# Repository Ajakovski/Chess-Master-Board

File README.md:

<div align="center">

# A Standalone PCB Chess Board with OnBoard Machine

### _A chess board that sees every piece, lights every move, and thinks alongside you - no external modules required._

</div>

---

# Overview

**Chess Master Board**

With the power of electro-magnetism this master board is capable of reading every move that the players are making. The powerfull chip with the built in machine gives us the power of a ~2000 ELO player that computes the best moves ***within 2 seconds*** and finally the built in RGB LED matrix sends light signals towards the player with the best move suggestions for you to beat every opponent.

A completely standalone project that requires no external connection gives us the ability to use this board anywhere that we want to. Thanks to the sleep-mode option we recieve a massive battery life extention and we can move on with the game just in case if we decided to pause it.

The chess machine follows every official chess rule and it has included every possible recommendation pattern thanks to the RGB LED matrix. Just put the pieces on their starting squares, press the two buttons for a short period of time and ***ENJOYYY***

Built as an open-source hardware product - every schematic, PCB file and line of firmware is available to reproduce, modify and improve.

---

# Zine

<div align="center">

</div>

---

# Motivation

Some people (like me :)) want to play the game in real life but seem to lack the power of quick decision making while they lose to their opponent. Ofcourse you can achieve that on your smartphone or a PC with a helper like stockfish but what if you dont want to use your digital hardware for playing the game???

With that issue on my mind i created **Chess Master Board** with a different concept:

> _What if the board itself was the computer?_

**The helping buddy that you need!** Hidden inside of the medium sized chess board with just a 5 second double hold on the buttons you awake the mastermind that will help you againts any enemy.

The design is inspired by the tactile satisfaction of phisical chess and will to win your opponents while they struggle for survial:

- No screen needed - the board communicates through light
- No IoT connection needed - the engine runs entirely on device
- Shipped and open-sourced product so anyone can build it, modify it and improve it

The project is also an increidible journey into embedded hardware and PCB design for any enthusiast willing to endulge himself into the type of engineering.

---

# Assembly Guide

## Hardware

***Notice: Always follow the order Main→Upper→Clock PCB for assembling the hardware***

***A visual representation of the whole project has been given with the file:***

***If you dont prefer via the files you can always refer to the visual representation via [OnShape](https://cad.onshape.com/documents/13dd493447813ae98dcbc5b6/w/f13770b66ce0189c65580405/e/d896ca2ed77523ba709b8a3c?renderMode=0&uiState=6a33bc9ec68ee69fbb85f0c4).***

```bash
Hardware/FULLY_ASSEMBLED_PROJECT.step
```

### 1. Order the PCBs and 3D Model

Navigate to: (For PCBs)

```bash
Hardware/KiCad/Gerbers/
```

*Upload the included Gerber files to your preferred PCB manufacturer and order the boards.*

Navigate to: (For 3D Model)
```bash
Hardware/3D_Printing/ (Both zip files)
```
Due to github memory restrictions they are split into 2 files. G-code Pieces features the black/white collection of pieces ready for printing and the V3 Chess 3D.zip is equipped with the full set of information and g-code files for printing the board.
There is also a step version of the files from V3 Chess 3D.zip file, use those also if you need them.

*Upload the G-Code files to your preferred manufacturer and order the parts.*

*The latest version is recommended but if you prefer any older version feel free to use it.*

### 2. Order the Components

Whether you want to order it trough a PCBA concept or to solder it manually you should refer to the BOM file.

```bash
Hardware/BOM.csv
Hardware/Component Libraries.zip
```
All of the files for the components are placed into a zip file due to memory constraints.

Order all parts before starting your assembly and sort them out because there will be a lot of them.

### 3. Solder SMD Components

Considering that you have chosen to solder them personally you should follow the following steps:

Start with the smallest SMD passives before moving to ICs (Refer to the schematic alway before soldering):

- All 0402 decoupling capacitors (100nF) across the board
- Bulk capacitors (1μF, 4.7μF, 10μF, 22μF) near power Ics
- USB-C CC resistors (5.1KΩ)
- All signal and bias resistors per schematic

Recommended tools:
- Flux
- A strong soldering iron with a fine-tip
- Tweezers
- Solder paste + hot air
- Helping hands with a magnifying glass

### 4. Solder Power ICs

Solder the power subsystem in order - validate each stage before starting the next:

- **U3** (BQ24074RGT) - Li-Ion charger, VQFN-16. Solder with hot air; confirm EPAD contact/
- **TH1** (NTC thermistor) - battery temperature input for the charger IC
(Notice: If you are unable to find an NTC thermisto, a 10K ohm resistor will work just fine as a subsitude)
- **U4** (TPS61023DRLT) + **1uH1** (XEL4030-102MEC) - 5V boost converter for LED rail.
- **U5** (AP2112K-3.3TRG1) - 3.3V LDO for ESP32 and logic
- **U145, U146** (REUF300) - PTC resettable fuses on power rails
- **U144** (USBLC6-2P6) - USB ESP protection
- **J2** (USB4110GFA) - USB-C receptacle 
- **D1, D2** - charging status LEDs

Verify whether 5V and 3.3V rails are correct before including anything else.

### 5. Solder the Sensor and Shift Register Array

- **U79-U142** - 64x AH1806-W-7 hall effect sensors (SOT-23, active-LOW)
- **U6-U13** - 8 74HC165BQ shift registers (SSOP-16/QFN, daisy chained)
- Verify sensor orientation - pin 1 marker must align with PCB silkscreen

### 6. Solder the LED Array

- **U14-U77** - 64x APA102C RGB LEDs (5050)
- Theese are orientations-sensitive - follow the schematic and confirm the cathode corner marker before placing every row
- Ensure every LED sits completely flat before reflow; a lifted pad will break the entire following part of the chain.

### 7. Solder the Level Shifter

- **U143** (SN74AHCT125D) - bridges the ESP32's 3.3V outputs to the 5V APA102C DATA and CLK lines
- Without this component the APA102C will be under constant failirue.

### 8. Install the ESP32-S3 Module

- Solder **U1** (ESP32-S3-WROOM2) onto its castellated pads.
- The antenna area requires a **15mm keepout zone** on the base PCB - no copper, no vias (except the screw nearby).
- Confirm the via grid under the module makes solid contact with all EPAD ground pads

### 9. Install the Display and Connectors
- **DS2** - 2.23" 128x32 OLED, I²C interface
- **J1/J4 on Main PCB** Samtec ZF1-15-92-X-WT-X board connectors
- **J3 on Upper PCB** Samtec ZF1-15-92-X-WT-X board connectors
- **J7 on Clock PCB** Samtec ZF1-15-92-X-WT-X board connectors

### 10. Install User Interface Components

- **S3, S4** (TL3315NF250Q) - player clock buttons
- **SW2** (Omron B3FS) - Boot button

### 11. Install Battery Holders and Cells

- Solder **BT1, BT2** (Keystone 1043) - 18650 cell holders
- Do not insert cells untill all soldering is fully complete
- Confirm polarity markings on PCB silkscreen before inserting cells

### 12. Assemble the Enclosure

***Materials needed for assembling:***

- 32x Neodymium magnet in circle with dimensions: 20mm diameter x 5mm height
- 6x Neodymium magnet in a rectangle with dimensions 5x10x2mm
- Glue, any type just make sure to get a strong one
- 11x M3 screw nuts (more is fine in case you loose some)
- Notice: If you dont get screws with the OLED screen you will have to acquire them personally

***Steps for assembling***

The main part of the assembling is sticking the magnets in their appropriate places. 
There are 2 places where they should be placed:
- The rectangular magnets should be placed 3x on the lid used for closing the bottom of the chess board where on one side you will find 3 rectangular holes and 3x inside of the chess board where you will the same 3 rectangular insertions. Apply glue inside of them and stick the magnets inside. **BE CAREFUL** and place the pair of three magnets with opposite polarities. So if the closing lid has the north pole facing outwards, make sure to have the south pole facing outwards on the chess board.
- The circular magnets are designated to go into the chess pieces. Same procedure, apply glue and stick them. **Make sure to place the south pole outwards because otherwise the hall effect sensors will have a poor reading**
- Every PCB has their own designated screw holes and how they should be placed. **Every PCB next to the screw hole has the side on where it should be placed.** (for eg. UR- Upper Right, DR - Down Right)
- The Push buttons should be inserted from inside of the chess board before putting the screws on for the Clock PCB so that the buttons stay locked on top of the buttons built-in on the PCB.
- Verify detection by powering the board and placing every piece on their starting square during first boot.

---

## Firmware Installation

### 1. Install ESP-IDF

```bash
git clone --recursive https://github.com/espressif/esp-idf.git ~/esp/esp-idf
cd ~/esp/esp-idf
./install.sh esp32s3
source ./export.sh
```

Follow the [official Espressif guide](https://docs.espressif.com/projects/esp-idf/en/stable/esp32s3/get-started/index.html) for WIndows and macOS variants.

### 2. Clone the Repository

```bash
git clone https://github.com/Ajakovski/chess-master-board.git
cd chess-master-board
cd Firmware
```

### 3. Set Target and Build

```bash
idf.py set-starget esp32s3
idf.py build
```

### 4. Flash the Firmware

Connect via USB-C. If the board does not enter download mode automatically, hold **BOOT** and tap **EN**, then release BOOT.

```bash
# Linux
idf.py -p /dev/tty/USB0 flash

# macOS
idf.py -p /dev/cu.usbserial-XXXX flash

# Windows
idf.py -p COM3 flash
```

### 5. Monitor Serial Output

```bash
idf.py -p /dev/ttyUSB0 monitor
```

Exit with 'Ctrl+]'.

---

# BOM

**If you are refering from the BOM.csv file please use a converter csv to table because it will be hard for you to read the documentation. And as always you can recall from my githubs BOM anytime you want**

| Designator | Function | Value / Part | Package | Qty | Price (USD) | Link |
|---|---|---|---|---|---|---|
| U1 | MCU Module | ESP32-S3-WROOM-2 N32R16V | LCC-54 | 1 | $12 | [Mouser](https://www.mouser.bg/ProductDetail/Espressif-Systems/ESP32-S3-WROOM-2-N32R16V?qs=%252BHhoWzUJg4Kf%2FwmS40wg%252BQ%3D%3D&srsltid=AfmBOopjud5fwNEdPJr_Fcp_F6RRXBi_0mpNTvMmjx49w7TWEqiv5xGV) |
| U79–U142 | Hall Effect Sensor | AH1806-W-7 | SOT-23 | 64 | $20 | [Mouser](https://www.mouser.com/ProductDetail/Diodes-Incorporated/AH1806-W-7?qs=eSfX1CQlHqqRKgthoXGrzg%3D%3D&srsltid=AfmBOoqvt9XKLP8jc6GHH0L_jmNus1_TszQpJJyJu60i3bDtAeJsRl4r) |
| U6–U13 | Shift Register | 74HC165BQ_115 | QFN-17 | 8(10) | $2.21 | [Mouser](https://www.mouser.bg/ProductDetail/Nexperia/74HC165BQ115?qs=P62ublwmbi86viaf9iloMA%3D%3D&srsltid=AfmBOop67e87aW457vff1BOXmou8TWC8JPC6vrp5882xNvyS27eVy15c) |
| U14–U77 | Addressable RGB LED | APA102C | SON-6 (5050) | 64(100) | $10.5 | [AliExpress](https://www.aliexpress.com/item/1005008174203527.html) |
| U143 | Level Shifter | SN74AHCT125DR | SOIC-14 | 1 | $0.46 | [Mouser](https://www.mouser.bg/ProductDetail/Texas-Instruments/SN74AHCT125DR?qs=B7lSdIxWQkm9VQkJOjfRaA%3D%3D) |
| DS2 | OLED Display | 128×32 2.23" I²C | SSD1305 | 1 | $10 | [AliExpress](https://www.aliexpress.com/item/1005008489357042.html?spm=a2g0o.productlist.main.9.1cd31P5n1P5nfd&algo_pvid=10006fad-7505-426f-8c02-2c3dbc745dfc&algo_exp_id=10006fad-7505-426f-8c02-2c3dbc745dfc-8&pdp_ext_f=%7B%22order%22%3A%229%22%2C%22eval%22%3A%221%22%2C%22fromPage%22%3A%22search%22%7D&pdp_npi=6%40dis%21MKD%21567.22%21567.22%21%21%2165.40%2165.40%21%40212e520f17815127163675148eea9b%2112000045367691230%21sea%21MK%210%21ABX%211%210%21n_tag%3A-29910%3Bd%3Aaeed944%3Bm03_new_user%3A-29895&curPageLogUid=1Bi8k4hGK8K7&utparam-url=scene%3Asearch%7Cquery_from%3A%7Cx_object_id%3A1005008489357042%7C_p_origin_prod%3A#nav-description) |
| BT1, BT2 | 18650 Battery Holder | Keystone 1043 | THT | 2 | $6.82 | [Mouser](https://www.mouser.com/ProductDetail/Keystone-Electronics/1043?utm_campaign=mouser&qs=%2F7TOpeL5Mz6j%2FnxeOA1rsg%3D%3D&utm_medium=online&utm_source=snapedaonline&utm_content=modelunipart_id=214578&manufacturer=Keystone) |
| U3 | Li-Ion Charger IC | BQ24074RGT | VQFN-16 | 1 | $2.48 | [Mouser](https://www.mouser.bg/ProductDetail/Texas-Instruments/BQ24074RGTR?qs=ZV%2Fxhq4oszp2Nll7fIx5wg%3D%3D&srsltid=AfmBOopf_GDP2yO0D5PAa7cuepwFxpUxXFdTjUaKyMCHw1c4K6qqB7_Z) |
| U4 | Boost Converter (5V) | TPS61023DRLT | SOT-6 | 1 | $1.4 | [Mouser](https://www.mouser.bg/ProductDetail/Texas-Instruments/TPS61023DRLT?qs=BJlw7L4Cy78Zr3IJIU3gNw%3D%3D) |
| 1uH1 | Power Inductor | XEL4030-102MEC (1µH) | XEL4030 | 1 | $2.17 | [Mouser](https://www.snapeda.com/api/url_track_click_mouser/?unipart_id=4653188&manufacturer=Coilcraft&part_name=XEL4030-102MEC&search_term=None) |
| U5 | 3.3V LDO Regulator | AP2112K-3.3TRG1 | SOT-25 | 1 | $0.25 | [Mouser](https://www.mouser.bg/ProductDetail/Diodes-Incorporated/AP2112K-3.3TRG1?qs=x6A8l6qLYDDPYHosCdzh%2FA%3D%3D) |
| U144 | USB ESD Protection | USBLC6-2P6 | SOT-666 | 1 | $0.63 | [Mouser](https://www.mouser.bg/ProductDetail/STMicroelectronics/USBLC6-2P6?qs=6ARB0lp6jlViGcbUSvj1Mw%3D%3D) |
| U145, U146 | PTC Resettable Fuse | RUEF300 (3A) | Radial | 2 | $1 | [AliExpress](https://www.aliexpress.com/item/1005003699936643.html?spm=a2g0o.productlist.main.2.1515qUETqUETL7&algo_pvid=1ab326b7-57ac-4a5e-9c91-1f0688d12436&algo_exp_id=1ab326b7-57ac-4a5e-9c91-1f0688d12436-1&pdp_ext_f=%7B%22order%22%3A%2269%22%2C%22eval%22%3A%221%22%2C%22fromPage%22%3A%22search%22%7D&pdp_npi=6%40dis%21MKD%2140.94%2140.94%21%21%210.70%210.70%21%402101529317817805763092080ee682%2112000026854019128%21sea%21MK%210%21ABX%211%210%21n_tag%3A-29910%3Bd%3Acd05e435%3Bm03_new_user%3A-29895&curPageLogUid=hEJCwyMy2faS&utparam-url=scene%3Asearch%7Cquery_from%3A%7Cx_object_id%3A1005003699936643%7C_p_origin_prod%3A) |
| TH1 | NTC Thermistor | NTCG103JF103FT1S | 0402 | 1 | $0.11 | [Mouser](https://www.mouser.bg/ProductDetail/TDK/NTCG103JF103FT1S?qs=cNoPOocMWw11FEwwc%2F4vOg%3D%3D) |
| J2 | USB-C Receptacle | USB4110GFA | SMD | 1 | $1.27 | [Mouser](https://www.mouser.com/ProductDetail/GCT/USB4110-GF-A?qs=KUoIvG%2F9IlYiZvIXQjyJeA%3D%3D&srsltid=AfmBOoqFJ-91enIyu9A26tSaC9mGIXgz0BrHN1BArDjjXIR4G4HD0bAR) |
| J1, J3, J4, J7 | Board Connector | Samtec ZF1-15-02-X-WT-X | SMD | 4 | $6.8 | [Mouser](https://www.mouser.bg/ProductDetail/Samtec/ZF1-15-02-TM-WT?qs=%252BZP6%2F%252BtExtBQirvzLIJzEA%3D%3D) |
| S3, S4 | Player Clock Button | TL3315NF250Q | SMD | 2 | $0.28 | [Mouser](https://www.mouser.bg/ProductDetail/E-Switch/TL3315NF250Q?qs=g35H13458Kaz43%252B3owu1iQ%3D%3D) |
| SW2 | Boot Switch | Omron B3FS | SMD | 1 | €0.62 | [Mouser](https://www.mouser.bg/ProductDetail/Omron-Electronics/B3FS-1000P?qs=ImaqFqjHA4k6odVF2%2FXWpQ%3D%3D) |
| D1, D2 | Charging LED | Q65111A7377 | 0402 | 2 | $0.92 | [Mouser](https://www.mouser.com/ProductDetail/ams-OSRAM/Q65111A7377?qs=sGAEpiMZZMv0DJfhVcWlKwb9uSCDLxPf%2FYHVt4kOg1XhmEL4WLxLEQ%3D%3D) |
| R3, R4 | USB-C CC Resistor | 5.1kΩ | 0402 | 2 | $0.20 | [Mouser](https://www.mouser.bg/ProductDetail/YAGEO/RC0402FR-075K1L?qs=YUgVZYePFqCSmQuaha43RA%3D%3D) |
| R5 | Charge Current Set | 800Ω | 0402 | 1 | $0.10 | [Mouser](https://www.mouser.bg/ProductDetail/SEI-Stackpole/RMCF0402FT806R?qs=IPgv5n7u5Qa32gYJEFJiUQ%3D%3D) |
| R6 | Charge Set | 1.2kΩ | 0402 | 1 | $0.10 | [Mouser](https://www.mouser.bg/ProductDetail/YAGEO/RC0402JR-071K2L?qs=KuCtQF8z8nDVvRd2gRh7cw%3D%3D) |
| R7, R107, R108 | Charge Set | 2kΩ | 0402 | 3 | $0.30 | [Mouser](https://www.mouser.bg/ProductDetail/YAGEO/RC0402FR-072KL?qs=V1yeUXFNrkkvY0qFpE7ijg%3D%3D) |
| R8, R11, R13, R35, R36 | Pull / Bias | 100kΩ | 0603 | 5 | $0.50 | [Mouser](https://www.mouser.bg/ProductDetail/YAGEO/RC0603FR-07100KL?qs=e1ok2LiJcmaihem8Va5%2Fsw%3D%3D) |
| R9 | Pull / Bias | 100kΩ | 0402 | 1 | $0.10 | [Mouser](https://www.mouser.bg/ProductDetail/YAGEO/RC0402FR-07100KL?qs=mnq%2FyloZIXzTlUn7JAHSWg%3D%3D) |
| R12 | Bias | 750kΩ | 0805 | 1 | $0.10 | [Mouser](https://www.mouser.bg/ProductDetail/Bourns/CR0805-FX-7503ELF?qs=Ek4EPvi0xiD1ZaaiTWdU0w%3D%3D) |
| R10 | Current Limit | 330Ω | 0402 | 1 | $0.10 | [Mouser](https://www.mouser.bg/ProductDetail/YAGEO/RC0402FR-07330RL?qs=V1yeUXFNrkngRWHRQxns%2Fg%3D%3D) |
| R16–R19, R23, 39,40, R43, R44, R45-R106 | Pull-up / Pull-down | 10kΩ | 0402 | 71 | $0.77 | [Mouser](https://www.mouser.bg/ProductDetail/YAGEO/AC0402FR-0710KL?qs=yhV1fb9g%2FKYkR5U3B7upEQ%3D%3D) |
| R34 | Pull-up / Pull-down | 10kΩ | 0201 | 1 | $0.10 | [Mouser](https://www.mouser.bg/ProductDetail/YAGEO/RC0201FR-0710KL?qs=FLc6udek5PS1AiJCgpc6bQ%3D%3D) |
| R14, R15, R22, R24, R25, R30, R31, R41, R42 | Series Damping | 33Ω | 0402 | 9 | $0.9 | [Mouser](https://www.mouser.bg/ProductDetail/YAGEO/RC0402JR-0733RL?qs=uM1JSSdPjOAuJ%2F4ZF3IeKA%3D%3D) |
| R37 | Voltage-divider | 3.3kΩ | 0402 | 1 |$0.1 | [Mouser](https://www.mouser.bg/ProductDetail/YAGEO/RC0402JR-103K3L?qs=qpJ%252B%252B%252Bdg6p211Yj14a%2Fidg%3D%3D)
| R38 | Voltage-divider | 6.8kΩ | 0402 | 1 |$0.27 | [Mouser](https://www.mouser.bg/ProductDetail/Panasonic/ERJ-H2RD6801X?qs=sGAEpiMZZMtlubZbdhIBIGXWvNSLmQjepnVQul72bkc%3D)
| C (various) | Decoupling / Bulk | 100nF, 1µF, 4.7µF, 10µF, 22µF | 0402/0603/0805/1206 | 105 | $16 | [Amazon](https://www.amazon.com/Bridgold-111Types-Capacitor-1pF-10uF-3-9pF-22uF/dp/B0C196FBK3/ref=sr_1_10?dib=eyJ2IjoiMSJ9.Sik-1N6T3B22pMHx3gZwssQe9HV9aXahGuDaX-uB1yfBLuMOqud5ObrWRTFUEP5qQT2cI_n6L6fgTxfF61UY6m7jwAR2JlYfwWtNi5UCKX4QVam3zu4P14UT01DyXCllphzxt5CmLBpMIcKJr-lpdFgCHgOWfw1AMDWRa0VJgoOHSTB1Ejcqxwg_bRNHyVE3csjNCQKdCS_s7IOfQRityBtC0y6ZoSuw4EYrFxCoT9w.R-0uFALOYO601m_UiLGERn05S21OQveJX7LUG-RrBD0&dib_tag=se&keywords=SMD%2BCapacitor&qid=1781345348&sr=8-10&th=1) |
| C17, C18 | CP_EIA-7343-20_Kemet-V | 100µF | 2917 | 2 | $8.68 | [Mouser](https://www.mouser.bg/ProductDetail/KEMET/T494V107K016AT?qs=esDHISMOsl1F06bDLafyPA%3D%3D) |
| Neodymium magnets | Circle | N35-N52 | 20x5cm | 32(40) | $20 | [Amazon](https://www.amazon.com/TRYMAG-Decorative-Neodymium-Powerful-Scientific/dp/B0G4D78X7T/ref=pd_ci_mcx_di_int_sccai_cn_d_sccl_1_7/136-7378115-7020437?pd_rd_w=JVAsz&content-id=amzn1.sym.751acc83-5c05-42d0-a15e-303622651e1e&pf_rd_p=751acc83-5c05-42d0-a15e-303622651e1e&pf_rd_r=S49NM63KZQJV9PRHP6W2&pd_rd_wg=72OFc&pd_rd_r=0b37500f-f078-4104-9d5c-44c4b33a4363&pd_rd_i=B0FG839Q2X&th=1) | 
| Neodymium magnets | Rectangular | N35-N52 | 5x10x2mm | 6(100) | $7.6 | [Amazon](https://www.amazon.com/dp/B0GK8XXS5P/ref=sspa_dk_detail_right_aax_0?sp_csd=d2lkZ2V0TmFtZT1zcF9kZXRhaWxfcmlnaHRfc2hhcmVk&th=1) |
| BT1, BT2 | Li-ion Battery  | 3.7V 3400mAh | 18650 | 2 | $5.76 (I have them) | [AliExpress](https://www.aliexpress.com/item/1005008704323807.html?spm=a2g0o.productlist.main.11.41426338JMDLOG&algo_pvid=5468ca2c-7ea9-4975-b4e9-84117a248739&algo_exp_id=5468ca2c-7ea9-4975-b4e9-84117a248739-10&pdp_ext_f=%7B%22order%22%3A%22594%22%2C%22eval%22%3A%221%22%2C%22fromPage%22%3A%22search%22%7D&pdp_npi=6%40dis%21MKD%21589.61%21306.60%21%21%2168.00%2135.36%21%40212a70c017813517499738402e1745%2112000046318715827%21sea%21MK%210%21ABX%211%210%21n_tag%3A-29910%3Bd%3Aaeed944%3Bm03_new_user%3A-29895&curPageLogUid=c8XERDHzRrxn&utparam-url=scene%3Asearch%7Cquery_from%3A%7Cx_object_id%3A1005008704323807%7C_p_origin_prod%3A)
| X | FFC Connector | 15-pin | 500mm | 3 | $6.82 | [Amazon](https://www.amazon.com.be/-/en/Flexible-Ribbon-Cable-Camera-Module/dp/B07P8Z27ZY?language=en_GB)|
| X | M3 Screws | M3 | 10mm | 50 | $5.5 | [AliExpress](https://www.aliexpress.com/item/33028169759.html?spm=a2g0o.productlist.main.48.53865b5fAhCGwY&algo_pvid=629709d9-a21f-428c-aced-7c4376ca24fc&algo_exp_id=629709d9-a21f-428c-aced-7c4376ca24fc-45&pdp_ext_f=%7B%22order%22%3A%22366%22%2C%22eval%22%3A%221%22%2C%22fromPage%22%3A%22search%22%7D&pdp_npi=6%40dis%21AED%215.37%213.75%21%21%211.42%210.99%21%402102f0cc17811144146558226e9158%2112000025630870148%21sea%21AE%216550317333%21ABX%211%210%21n_tag%3A-29910%3Bd%3A9c10be3c%3Bm03_new_user%3A-29895%3BpisId%3A5000000204469934&curPageLogUid=FOQQuqUMxISX&utparam-url=scene%3Asearch%7Cquery_from%3A%7Cx_object_id%3A33028169759%7C_p_origin_prod%3A&gatewayAdapt=ara2glo) |
| X | M3 Nuts | M3 | | 25 | $3.5 | [AliExpress](https://www.aliexpress.com/item/32978551452.html?spm=a2g0o.productlist.main.1.7c154ece9D2Th2&algo_pvid=84088476-8a89-43b9-a92f-5755b7a463e3&algo_exp_id=84088476-8a89-43b9-a92f-5755b7a463e3-0&pdp_ext_f=%7B%22order%22%3A%222796%22%2C%22eval%22%3A%221%22%2C%22fromPage%22%3A%22search%22%7D&pdp_npi=6%40dis%21MKD%21254.64%21254.06%21%21%214.36%214.35%21%40210156fc17816089059113153e1450%2112000015835866719%21sea%21MK%210%21ABX%211%210%21n_tag%3A-29910%3Bd%3Aaeed944%3Bm03_new_user%3A-29895&curPageLogUid=wct4KENxKUYh&utparam-url=scene%3Asearch%7Cquery_from%3A%7Cx_object_id%3A32978551452%7C_p_origin_prod%3A)|
| X | Main PCB | PCBWAY as second alternative | |5|70$|[JLCPCB](https://jlcpcb.com/)|
| X |Upper PCB| | |5|130$|[JLCPCB](https://jlcpcb.com/)|
| X |Clock PCB| PCBWAY as second alternative | |5|58$|[JLCPCB](https://jlcpcb.com/)|
| X |Main Chess Board 3D| | |1|$80|[3dprintmk](https://www.3dprintmk.com)|
| X |Chess Board Lid 3D| | |1|$15|[3dprintmk](https://www.3dprintmk.com)|
| X |Buttons 3D| | |2|$7.5|[3dprintmk](https://www.3dprintmk.com)|
| X |Chess Pieces 3D| | |2|$15|[3dprintmk](https://www.3dprintmk.com)|
| *Mouser Total* | $105| with cargo  | | | | | |
| *Amazon Total* | $71.79 | with cargo  | | | | | |
| *AliExpress Total* | $56 | with cargo  | without batteries | | | | |
| *PCB Printing* | $332 | with cargo | | | | | | 
| *3D Printing* | $120 | with cargo | | | | | |
| **TOTAL** | *approx. $680* | | | | | |
 
*Notice: Theese shipping costs are for a 3rd world country so if you are from the EU or USA there are high chances of having lower shipping costs*

*Notice: These are just recommendations that i have found to be secure and hopefully the cheapest option. Do your own research if you think that better deals exist on the current market depending on when you are buying it.*

---

# Features

- **Piece Detection** - 64 hall effect sensors, one per square and magnets inside the chess pieces
- **RGB LED Feedback** - the guide for your victory, shows active checks, best move and more!
- **Onboard Chess Engine** - mcu-max, ~2000 ELO at depth 8-10
- **Dual Player Clocks** - dedicated hardware button per player
- **OLED Display** - cool visual representation of time left, current player, machine state and battery percentage
- **18650 Battery Powered** - dual Li-Ion with onboard USB-C charging
- **Deep Sleep** - power saving mode and game state retained in RTC memory across scleep cycles
- **Protected Power Rails** - PTC fuses and USB ESD protection on all external-facing lines
- **Fully Custom PCB** - designed for shipping standards
- **Open Source** - complete hardware + firmware available
- **Closing Lid** - high quality lid with magnets for a neat experience if you decide to change the batteries

---

# Hardware Stack

| Subsystem | Component | Description |
|---|---|---|
| MCU | ESP32-S3-WROOM2 | 32MB Flash, 16MB PSRAM, Xtensa LX7 dual-core |
| Sensors | AH1806-W-7 x 64 | Active-LOW hall effect, SOT-23|
| Sensor Interface | 74HC165BQ x 8 | Parallel-in shift registers, daisy-chained |
| LEDs | APA102C x 64 | Addressable RGB, SPI-compatible, 5V |
| Level Shifter | SN74AHCT125D | 3.3V → 5V for APA102C DATA + CLK |
| Display | 128x32 OLED 2.23' | I²C Interface |
| Battery | Li-Ion 18650 batteries | |
| Charger | BQ2407RGT | Single-cell Li-ion, USB-C input, NTC-monitored |
| 5V Rail | TPS61023DRLT + XEL4030-102MEC | Boost converter for LED chain |
| 3.3V Rail | AP2112K-3.3TRG1 | LDO for ESP32 and logic |
| USB Protection | USBLC6-2P6 | ESD protection on USB-C lines |
| Fusing | REUF300 x 2 | 3A PTC resetable fuses on power rails |
| Firmware | ESP-IDF (FreeRTOS) | C, HAL + state machine architecture |
| Chess Engine | mcu-max | MIT, pure C, negamax + alpha-beta, depth 8 |

---

# PCB Design

The PCB was designed specifically for this project and its layout.

Key design requirements met:
- Via grid under module EPAD for grounding and thermal performance
- Shared GPIO12 clock routing for APA102C chain and 74HC165 shift register chain
- Integrated external pull-up for GPIO3
- Passive components placed per Espressif hardware design guidelines
- USB-C CC resistors for correct sinking identification
- Charging temperature monitoring via NTC thermistor
- 3 individual PCBs communicating between FFC cables
- 2x4 Layered PCBs for great signal integrity and power supply troughout the whole board
- Every piece is precisely placed according to the 3D chess board for the best workfoll

## PCB Layout

### Main PCB

*Some pictures may have been deformed in order to adjust their dimensions*

### Upper PCB

### Clock PCB

## Schematic

***Refer to the PDF file for better overview*** [PDF](Pictures/Schematic_Print.pdf)

### Main PCB
#### MCU/IC section
 <br>
#### Power Management section

### Upper PCB

#### Hall Effect sensors

#### RGB LED Matrix

### Clock PCB

## Component Placement

<div align="center">

### Main PCB

### Upper PCB
 <br>

### Clock PCB

*Sorry for not including every 3D model (2.23" OLED, 2 push buttons and the BQ2407RGT charger). The folders that i managed to find from the web didn't have a 3D .step model*

</div>

---

# Enclosure
- Simple to assemble
- Firm and high-quality material for premium feel
- The board is made out of PETG material
- 100% fill on the top giving us crystal transparency for out LEDs
- Tolerances given accordingly
- Chess Pieces are made out of PLA

*Feel free to change the material type according to your desire but PETG is most recommended for transparency*

---

# Firmware (ESP-IDF)

Firmware features:
- FreeRTOS game state machine
- HAL drivers for all peripherals
- mcu-max chess engine integration (UCI interface, iterative deepening)
- Deep sleep with RTC memory retention
- Shared CLK sequencing between APA102C and 74HC165 chains

```bash
Chess-Master-Board/
|--- Firmware/
|    |--- main/
|        |--- hal/    # LED, sensor, OLED, button, battery drivers
|        |--- engine/ # mcu-max integration
|        |--- game/   # FreeRTOS state machine + chess rules
|        |--- main.c/
|    |--- CMakeLists.txt
|    |--- partitions.csv
|    |--- sdkconfig
|--- Hardware/
|    |--- 3D_Printing/
|    |--- KiCad/     
|    |--- BOM.csv 
|    |--- Component Libraries.zip 
|--- Pictures/
|--- LICENSE
|--- README.md
|--- Chess Master Board Zine.pdf
|--- chess-master-board-journal.md
```

---

# Current Status

- [X] Initial Concept
- [X] Layout Finalized
- [X] PCB Design
- [X] Schematic
- [X] Firmware - HAL Drivers
- [X] Firmware - Game State Machine
- [X] Chess Engine Integration
- [X] Deep Sleep + RTC Retention
- [X] Battery Monitoring
- [X] 3D Models
- [X] Final BOM
- [X] Create a Zine
- [X] Final Build
- [ ] Create an IoT Version
- [ ] Upgrade the 3D model
- [ ] Improve the PCBs
- [ ] Make different size variations

---

# Contributing

Contributions, suggestions and feedback are welcome!!!

If you'd like to improve Chess Master Board:

1. Fork or clone the repository
```bash
git clone https://github.com/Ajakovski/chess-master-board.git
cd chess-master-board
```

2. Create your feature branch (if forked)
3. Commit your changes
4. Open a pull request

For significant hardware changes, open an issue first to discuss before investing time in layout work. Any new HAL driver must be self-contained in its own `.c`/`.h` pair.

If you build one, open an issue with photos.

---

# Creator

### Ajakovski aka. Marsovac

Hey my name is Andrej and im from Macedonia, Kratovo. Im 17 years old and i really enjoy making cool project which are all posted on my github.

Main focus while building the project:
- Individual planning and structuring
- embedded systems engineering
- schematic construction and following electrical concepts
- first PCB construction EVER!!!
- phisical product design
- to participate Fallout from HackClub
- connect with other likewise enthusiasts
- chess

---

# License

This project is licensed under the **MIT License** - see [LICENSE](LICENSE) for full terms.

Chess engine: [mcu-max](https://github.com/Gissio/mcu-max) - MIT License

---

<div align="center">

## CHESS MASTER BOARD

### _Every move, illuminated._

</div>

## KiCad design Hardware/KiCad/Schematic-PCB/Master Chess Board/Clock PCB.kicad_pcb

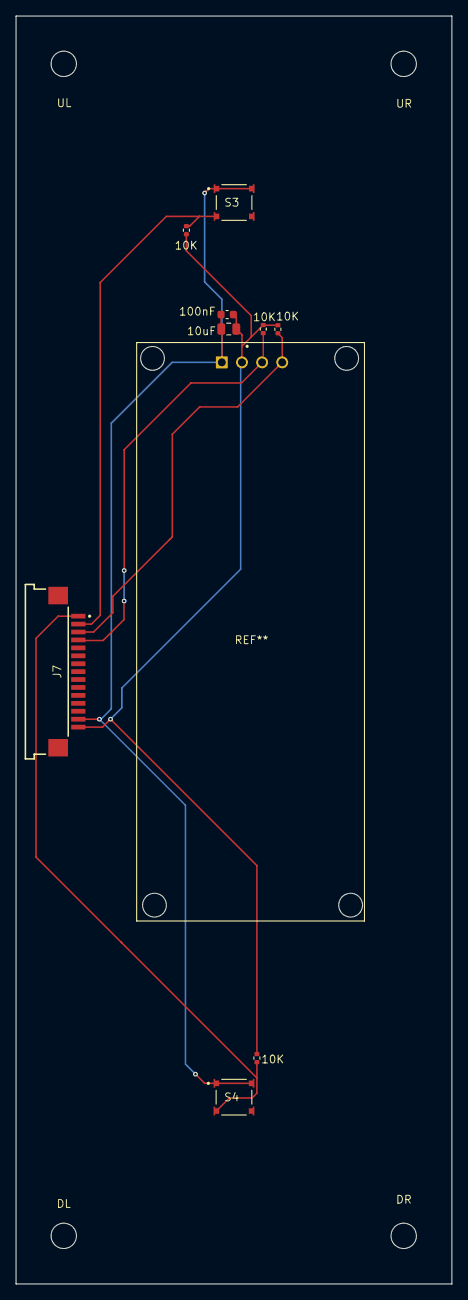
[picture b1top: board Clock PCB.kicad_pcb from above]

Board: 2 copper layers, 55.0 x 160.0 mm, 13 parts (0 on the bottom side), 6 nets.

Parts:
10Kohm, 10Kohm#2, 10Kohm#3, 10Kohm#4: R_0402_1005Metric
10uF: C_0805_2012Metric
100nF: C_0603_1608Metric
DL: MountingHole_3.2mm_M3
DR: MountingHole_3.2mm_M3
J7: ZF1-15-02-X-WT-X; SAMTEC_ZF1-15-02-X-WT-X
S3, S4: TL3315NF250Q; SW_TL3315NF250Q
UL: MountingHole_3.2mm_M3
UR: MountingHole_3.2mm_M3

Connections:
+3.3V: 10Kohm.2, 10Kohm#2.2, 10Kohm#3.2, 10Kohm#4.2, 10uF.2, 100nF.2, J7.15
/CLK I2C: 10Kohm#3.1, J7.04
/Clock PCB/Player 1 CLK: 10Kohm#2.1, J7.01, S4.3
/Clock PCB/Player 2 CLK: 10Kohm#4.1, J7.02, S3.3
/Clock PCB/SDA: 10Kohm.1, J7.03
GND: 10uF.1, 100nF.1, J7.14, S3.1, S3.2, S4.1, S4.2

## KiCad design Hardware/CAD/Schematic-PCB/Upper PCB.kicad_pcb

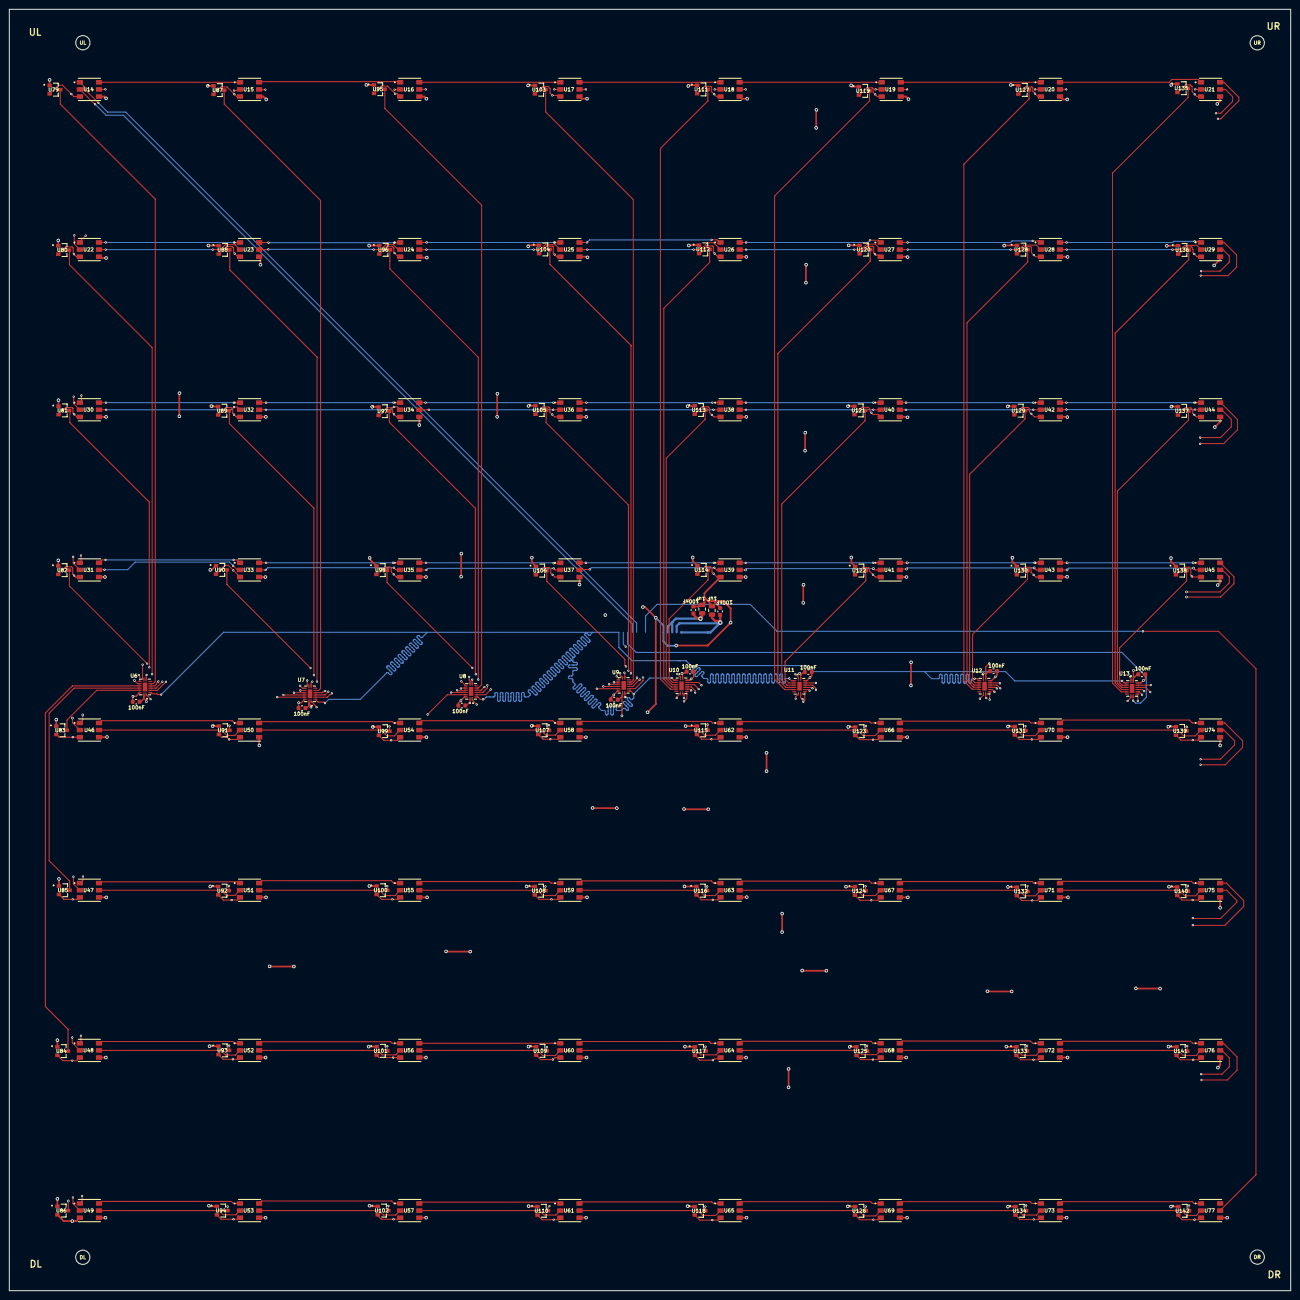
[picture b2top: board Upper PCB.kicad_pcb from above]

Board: 4 copper layers, 288.0 x 288.0 mm, 153 parts (1 on the bottom side), 206 nets.

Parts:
1uF, 1uF#2: C_0805_2012Metric
100nF, 100nF#2, 100nF#3, 100nF#4, 100nF#5, 100nF#6, 100nF#7, 100nF#8, 100nF#9, 100nF#10: C_0603_1608Metric
DL: MountingHole_3.2mm_M3
DR: MountingHole_3.2mm_M3
J3: ZF1-15-02-X-WT-X; SAMTEC_ZF1-15-02-X-WT-X
U6, U7, U8, U9, U10, U11, U12, U13: 74HC165BQ_115; QFN50P350X250X100-17N
U14, U15, U16, U17, U18, U19, U20, U21, U22, U23, U24, U25, U26, U27, U28, U29, U30, U31, U32, U33, U34, U35, U36, U37, U38, U39, U40, U41, U42, U43, U44, U45, U46, U47, U48, U49, U50, U51, U52, U53, U54, U55, U56, U57, U58, U59, U60, U61, U62, U63, U64, U65, U66, U67, U68, U69, U70, U71, U72, U73, U74, U75, U76, U77: APA102C; SON160P500X500X140-6N
U79, U80, U81, U82, U83, U84, U85, U86, U87, U88, U89, U90, U91, U92, U93, U94, U95, U96, U97, U98, U99, U100, U101, U102, U103, U104, U105, U106, U107, U108, U109, U110, U111, U112, U113, U114, U115, U116, U117, U118, U119, U120, U121, U122, U123, U124, U125, U126, U127, U128, U129, U130, U131, U132, U133, U134, U135, U136, U137, U138, U139, U140, U141, U142: AH1806-W-7; TRANS_SSM3J325F_LF
UL: MountingHole_3.2mm_M3
UR: MountingHole_3.2mm_M3

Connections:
+3.3V: 1uF.1, 100nF.2, 100nF#2.2, 100nF#3.2, 100nF#4.2, 100nF#5.2, 100nF#7.2, 100nF#8.2, 100nF#9.2, 100nF#10.2, J3.03, J3.04, U6.16 (VCC), U7.16 (VCC), U8.16 (VCC), U9.16 (VCC), U10.16 (VCC), U11.16 (VCC), U12.16 (VCC), U13.16 (VCC), U79.1 (VDD), U80.1 (VDD), U81.1 (VDD), U82.1 (VDD), U83.1 (VDD), U84.1 (VDD), U85.1 (VDD), U86.1 (VDD), U87.1 (VDD), U88.1 (VDD), U89.1 (VDD), U90.1 (VDD), U91.1 (VDD), U92.1 (VDD), U93.1 (VDD), U94.1 (VDD), U95.1 (VDD), U96.1 (VDD), U97.1 (VDD), U98.1 (VDD), U99.1 (VDD), U100.1 (VDD), U101.1 (VDD), U102.1 (VDD), U103.1 (VDD), U104.1 (VDD), U105.1 (VDD), U106.1 (VDD), U107.1 (VDD), U108.1 (VDD), U109.1 (VDD), U110.1 (VDD), U111.1 (VDD), U112.1 (VDD), U113.1 (VDD), U114.1 (VDD), U115.1 (VDD), U116.1 (VDD), U117.1 (VDD), U118.1 (VDD), U119.1 (VDD), U120.1 (VDD), U121.1 (VDD), U122.1 (VDD), U123.1 (VDD), U124.1 (VDD), U125.1 (VDD), U126.1 (VDD), U127.1 (VDD), U128.1 (VDD), U129.1 (VDD), U130.1 (VDD), U131.1 (VDD), U132.1 (VDD), U133.1 (VDD), U134.1 (VDD), U135.1 (VDD), U136.1 (VDD), U137.1 (VDD), U138.1 (VDD), U139.1 (VDD), U140.1 (VDD), U141.1 (VDD), U142.1 (VDD)
+5V: 1uF#2.1, 100nF#6.2, J3.01, J3.02, U14.4 (VCC), U15.4 (VCC), U16.4 (VCC), U17.4 (VCC), U18.4 (VCC), U19.4 (VCC), U20.4 (VCC), U21.4 (VCC), U22.4 (VCC), U23.4 (VCC), U24.4 (VCC), U25.4 (VCC), U26.4 (VCC), U27.4 (VCC), U28.4 (VCC), U29.4 (VCC), U30.4 (VCC), U31.4 (VCC), U32.4 (VCC), U33.4 (VCC), U34.4 (VCC), U35.4 (VCC), U36.4 (VCC), U37.4 (VCC), U38.4 (VCC), U39.4 (VCC), U40.4 (VCC), U41.4 (VCC), U42.4 (VCC), U43.4 (VCC), U44.4 (VCC), U45.4 (VCC), U46.4 (VCC), U47.4 (VCC), U48.4 (VCC), U49.4 (VCC), U50.4 (VCC), U51.4 (VCC), U52.4 (VCC), U53.4 (VCC), U54.4 (VCC), U55.4 (VCC), U56.4 (VCC), U57.4 (VCC), U58.4 (VCC), U59.4 (VCC), U60.4 (VCC), U61.4 (VCC), U62.4 (VCC), U63.4 (VCC), U64.4 (VCC), U65.4 (VCC), U66.4 (VCC), U67.4 (VCC), U68.4 (VCC), U69.4 (VCC), U70.4 (VCC), U71.4 (VCC), U72.4 (VCC), U73.4 (VCC), U74.4 (VCC), U75.4 (VCC), U76.4 (VCC), U77.4 (VCC)
/Upper PCB/CLK 5V: J3.12, U14.2 (CI)
/Upper PCB/CP: J3.15, U6.2 (CP), U7.2 (CP), U8.2 (CP), U9.2 (CP), U10.2 (CP), U11.2 (CP), U12.2 (CP), U13.2 (CP)
/Upper PCB/MISO RGB: J3.09, U77.5 (CO)
/Upper PCB/MOSI: J3.11, U14.1 (DI)
/Upper PCB/PL: J3.14, U6.1 (~PL), U7.1 (~PL), U8.1 (~PL), U9.1 (~PL), U10.1 (~PL), U11.1 (~PL), U12.1 (~PL), U13.1 (~PL)
/Upper PCB/Q7: J3.13, U13.9 (Q7)
GND: 1uF.2, 1uF#2.2, 100nF.1, 100nF#2.1, 100nF#3.1, 100nF#4.1, 100nF#5.1, 100nF#6.1, 100nF#7.1, 100nF#8.1, 100nF#9.1, 100nF#10.1, J3.05, U6.8 (GND), U6.10 (DS), U6.15 (~CE), U7.8 (GND), U7.15 (~CE), U8.8 (GND), U8.15 (~CE), U9.8 (GND), U9.15 (~CE), U10.8 (GND), U10.15 (~CE), U11.8 (GND), U11.15 (~CE), U12.8 (GND), U12.15 (~CE), U13.8 (GND), U13.15 (~CE), U14.3 (GND), U15.3 (GND), U16.3 (GND), U17.3 (GND), U18.3 (GND), U19.3 (GND), U20.3 (GND), U21.3 (GND), U22.3 (GND), U23.3 (GND), U24.3 (GND), U25.3 (GND), U26.3 (GND), U27.3 (GND), U28.3 (GND), U29.3 (GND), U30.3 (GND), U31.3 (GND), U32.3 (GND), U33.3 (GND), U34.3 (GND), U35.3 (GND), U36.3 (GND), U37.3 (GND), U38.3 (GND), U39.3 (GND), U40.3 (GND), U41.3 (GND), U42.3 (GND), U43.3 (GND), U44.3 (GND), U45.3 (GND), U46.3 (GND), U47.3 (GND), U48.3 (GND), U49.3 (GND), U50.3 (GND), U51.3 (GND), U52.3 (GND), U53.3 (GND), U54.3 (GND), U55.3 (GND), U56.3 (GND), U57.3 (GND), U58.3 (GND), U59.3 (GND), U60.3 (GND), U61.3 (GND), U62.3 (GND), U63.3 (GND), U64.3 (GND), U65.3 (GND), U66.3 (GND), U67.3 (GND), U68.3 (GND), U69.3 (GND), U70.3 (GND), U71.3 (GND), U72.3 (GND), U73.3 (GND), U74.3 (GND), U75.3 (GND), U76.3 (GND), U77.3 (GND), U79.2 (GND), U80.2 (GND), U81.2 (GND), U82.2 (GND), U83.2 (GND), U84.2 (GND), U85.2 (GND), U86.2 (GND), U87.2 (GND), U88.2 (GND), U89.2 (GND), U90.2 (GND), U91.2 (GND), U92.2 (GND), U93.2 (GND), U94.2 (GND), U95.2 (GND), U96.2 (GND), U97.2 (GND), U98.2 (GND), U99.2 (GND), U100.2 (GND), U101.2 (GND), U102.2 (GND), U103.2 (GND), U104.2 (GND), U105.2 (GND), U106.2 (GND), U107.2 (GND), U108.2 (GND), U109.2 (GND), U110.2 (GND), U111.2 (GND), U112.2 (GND), U113.2 (GND), U114.2 (GND), U115.2 (GND), U116.2 (GND), U117.2 (GND), U118.2 (GND), U119.2 (GND), U120.2 (GND), U121.2 (GND), U122.2 (GND), U123.2 (GND), U124.2 (GND), U125.2 (GND), U126.2 (GND), U127.2 (GND), U128.2 (GND), U129.2 (GND), U130.2 (GND), U131.2 (GND), U132.2 (GND), U133.2 (GND), U134.2 (GND), U135.2 (GND), U136.2 (GND), U137.2 (GND), U138.2 (GND), U139.2 (GND), U140.2 (GND), U141.2 (GND), U142.2 (GND)
unnamed: U6.11 (D0), U86.3 (OUTPUT)
unnamed: U6.12 (D1), U84.3 (OUTPUT)
unnamed: U6.13 (D2), U85.3 (OUTPUT)
unnamed: U6.14 (D3), U83.3 (OUTPUT)
unnamed: U6.3 (D4), U82.3 (OUTPUT)
unnamed: U6.4 (D5), U81.3 (OUTPUT)
unnamed: U6.5 (D6), U80.3 (OUTPUT)
unnamed: U6.6 (D7), U79.3 (OUTPUT)
unnamed: U6.9 (Q7), U7.10 (DS)
unnamed: U7.11 (D0), U94.3 (OUTPUT)
unnamed: U7.12 (D1), U93.3 (OUTPUT)
unnamed: U7.13 (D2), U92.3 (OUTPUT)
unnamed: U7.14 (D3), U91.3 (OUTPUT)
unnamed: U7.3 (D4), U90.3 (OUTPUT)
unnamed: U7.4 (D5), U89.3 (OUTPUT)
unnamed: U7.5 (D6), U88.3 (OUTPUT)
unnamed: U7.6 (D7), U87.3 (OUTPUT)
unnamed: U7.9 (Q7), U8.10 (DS)
unnamed: U8.14 (D3), U99.3 (OUTPUT)
unnamed: U8.3 (D4), U98.3 (OUTPUT)
unnamed: U8.4 (D5), U97.3 (OUTPUT)
unnamed: U8.5 (D6), U96.3 (OUTPUT)
unnamed: U8.6 (D7), U95.3 (OUTPUT)
unnamed: U8.9 (Q7), U9.10 (DS)
unnamed: U10.11 (D0), U118.3 (OUTPUT)
unnamed: U10.12 (D1), U117.3 (OUTPUT)
unnamed: U10.13 (D2), U116.3 (OUTPUT)
unnamed: U10.14 (D3), U115.3 (OUTPUT)
unnamed: U10.3 (D4), U114.3 (OUTPUT)
unnamed: U10.4 (D5), U113.3 (OUTPUT)
unnamed: U10.5 (D6), U112.3 (OUTPUT)
unnamed: U10.6 (D7), U111.3 (OUTPUT)
unnamed: U9.9 (Q7), U10.10 (DS)
unnamed: U10.9 (Q7), U11.10 (DS)
unnamed: U11.11 (D0), U126.3 (OUTPUT)
unnamed: U11.12 (D1), U125.3 (OUTPUT)
unnamed: U11.13 (D2), U124.3 (OUTPUT)
unnamed: U11.14 (D3), U123.3 (OUTPUT)
unnamed: U11.3 (D4), U122.3 (OUTPUT)
unnamed: U11.4 (D5), U121.3 (OUTPUT)
unnamed: U11.5 (D6), U120.3 (OUTPUT)
unnamed: U11.6 (D7), U119.3 (OUTPUT)
unnamed: U11.9 (Q7), U12.10 (DS)
unnamed: U12.11 (D0), U134.3 (OUTPUT)
unnamed: U12.12 (D1), U133.3 (OUTPUT)
unnamed: U12.13 (D2), U132.3 (OUTPUT)
unnamed: U12.14 (D3), U131.3 (OUTPUT)
unnamed: U12.3 (D4), U130.3 (OUTPUT)
unnamed: U12.4 (D5), U129.3 (OUTPUT)
unnamed: U12.5 (D6), U128.3 (OUTPUT)
unnamed: U12.6 (D7), U127.3 (OUTPUT)
unnamed: U12.9 (Q7), U13.10 (DS)
unnamed: U13.11 (D0), U142.3 (OUTPUT)
unnamed: U13.12 (D1), U141.3 (OUTPUT)
unnamed: U13.13 (D2), U140.3 (OUTPUT)
unnamed: U13.14 (D3), U139.3 (OUTPUT)
unnamed: U13.3 (D4), U138.3 (OUTPUT)
unnamed: U13.4 (D5), U137.3 (OUTPUT)
unnamed: U13.5 (D6), U136.3 (OUTPUT)
unnamed: U13.6 (D7), U135.3 (OUTPUT)
unnamed: U14.5 (CO), U15.2 (CI)
unnamed: U14.6 (DO), U15.1 (DI)
unnamed: U15.5 (CO), U16.2 (CI)
unnamed: U15.6 (DO), U16.1 (DI)
unnamed: U16.5 (CO), U17.2 (CI)
unnamed: U16.6 (DO), U17.1 (DI)
unnamed: U17.5 (CO), U18.2 (CI)
unnamed: U17.6 (DO), U18.1 (DI)
unnamed: U18.5 (CO), U19.2 (CI)
unnamed: U18.6 (DO), U19.1 (DI)
unnamed: U19.5 (CO), U20.2 (CI)
unnamed: U19.6 (DO), U20.1 (DI)
unnamed: U20.5 (CO), U21.2 (CI)
unnamed: U20.6 (DO), U21.1 (DI)
unnamed: U21.5 (CO), U22.2 (CI)
unnamed: U21.6 (DO), U22.1 (DI)
unnamed: U22.5 (CO), U23.2 (CI)
unnamed: U22.6 (DO), U23.1 (DI)
unnamed: U23.5 (CO), U24.2 (CI)
unnamed: U23.6 (DO), U24.1 (DI)
unnamed: U24.5 (CO), U25.2 (CI)
unnamed: U24.6 (DO), U25.1 (DI)
unnamed: U25.5 (CO), U26.2 (CI)
unnamed: U25.6 (DO), U26.1 (DI)
unnamed: U26.5 (CO), U27.2 (CI)
unnamed: U26.6 (DO), U27.1 (DI)
unnamed: U27.5 (CO), U28.2 (CI)
unnamed: U27.6 (DO), U28.1 (DI)
unnamed: U28.5 (CO), U29.2 (CI)
unnamed: U28.6 (DO), U29.1 (DI)
unnamed: U29.5 (CO), U30.2 (CI)
unnamed: U29.6 (DO), U30.1 (DI)
unnamed: U30.5 (CO), U32.2 (CI)
unnamed: U30.6 (DO), U32.1 (DI)
unnamed: U31.2 (CI), U44.5 (CO)
unnamed: U31.5 (CO), U33.2 (CI)
unnamed: U31.1 (DI), U44.6 (DO)
unnamed: U31.6 (DO), U33.1 (DI)
unnamed: U32.5 (CO), U34.2 (CI)
unnamed: U32.6 (DO), U34.1 (DI)
unnamed: U33.5 (CO), U35.2 (CI)
unnamed: U33.6 (DO), U35.1 (DI)
unnamed: U34.5 (CO), U36.2 (CI)
unnamed: U34.6 (DO), U36.1 (DI)
unnamed: U35.5 (CO), U37.2 (CI)
unnamed: U35.6 (DO), U37.1 (DI)
unnamed: U36.5 (CO), U38.2 (CI)
unnamed: U36.6 (DO), U38.1 (DI)
unnamed: U37.5 (CO), U39.2 (CI)
unnamed: U37.6 (DO), U39.1 (DI)
unnamed: U38.5 (CO), U40.2 (CI)
unnamed: U38.6 (DO), U40.1 (DI)
unnamed: U39.5 (CO), U41.2 (CI)
unnamed: U39.6 (DO), U41.1 (DI)
unnamed: U40.5 (CO), U42.2 (CI)
unnamed: U40.6 (DO), U42.1 (DI)
unnamed: U41.5 (CO), U43.2 (CI)
unnamed: U41.6 (DO), U43.1 (DI)
unnamed: U42.5 (CO), U44.2 (CI)
unnamed: U42.6 (DO), U44.1 (DI)
unnamed: U43.5 (CO), U45.2 (CI)
unnamed: U43.6 (DO), U45.1 (DI)
unnamed: U45.5 (CO), U46.2 (CI)
unnamed: U45.6 (DO), U46.1 (DI)
unnamed: U46.5 (CO), U50.2 (CI)
unnamed: U46.6 (DO), U50.1 (DI)
unnamed: U47.2 (CI), U74.5 (CO)
unnamed: U47.5 (CO), U51.2 (CI)
unnamed: U47.1 (DI), U74.6 (DO)
unnamed: U47.6 (DO), U51.1 (DI)
unnamed: U48.2 (CI), U75.5 (CO)
unnamed: U48.5 (CO), U52.2 (CI)
unnamed: U48.1 (DI), U75.6 (DO)
unnamed: U48.6 (DO), U52.1 (DI)
unnamed: U49.2 (CI), U76.5 (CO)
unnamed: U49.5 (CO), U53.2 (CI)
unnamed: U49.1 (DI), U76.6 (DO)
unnamed: U49.6 (DO), U53.1 (DI)
unnamed: U50.5 (CO), U54.2 (CI)
unnamed: U50.6 (DO), U54.1 (DI)
unnamed: U51.5 (CO), U55.2 (CI)
unnamed: U51.6 (DO), U55.1 (DI)
unnamed: U52.5 (CO), U56.2 (CI)
unnamed: U52.6 (DO), U56.1 (DI)
unnamed: U53.5 (CO), U57.2 (CI)
unnamed: U53.6 (DO), U57.1 (DI)
unnamed: U54.5 (CO), U58.2 (CI)
unnamed: U54.6 (DO), U58.1 (DI)
unnamed: U55.5 (CO), U59.2 (CI)
unnamed: U55.6 (DO), U59.1 (DI)
unnamed: U56.5 (CO), U60.2 (CI)
unnamed: U56.6 (DO), U60.1 (DI)
unnamed: U57.5 (CO), U61.2 (CI)
unnamed: U57.6 (DO), U61.1 (DI)
unnamed: U58.5 (CO), U62.2 (CI)
unnamed: U58.6 (DO), U62.1 (DI)
unnamed: U59.5 (CO), U63.2 (CI)
unnamed: U59.6 (DO), U63.1 (DI)
unnamed: U60.5 (CO), U64.2 (CI)
unnamed: U60.6 (DO), U64.1 (DI)
unnamed: U61.5 (CO), U65.2 (CI)
unnamed: U61.6 (DO), U65.1 (DI)
unnamed: U62.5 (CO), U66.2 (CI)
unnamed: U62.6 (DO), U66.1 (DI)
unnamed: U63.5 (CO), U67.2 (CI)
unnamed: U63.6 (DO), U67.1 (DI)
unnamed: U64.5 (CO), U68.2 (CI)
unnamed: U64.6 (DO), U68.1 (DI)
unnamed: U65.5 (CO), U69.2 (CI)
unnamed: U65.6 (DO), U69.1 (DI)
unnamed: U66.5 (CO), U70.2 (CI)
unnamed: U66.6 (DO), U70.1 (DI)
unnamed: U67.5 (CO), U71.2 (CI)
unnamed: U67.6 (DO), U71.1 (DI)
unnamed: U68.5 (CO), U72.2 (CI)
unnamed: U68.6 (DO), U72.1 (DI)
unnamed: U69.5 (CO), U73.2 (CI)
unnamed: U69.6 (DO), U73.1 (DI)
unnamed: U70.5 (CO), U74.2 (CI)
unnamed: U70.6 (DO), U74.1 (DI)
unnamed: U71.5 (CO), U75.2 (CI)
unnamed: U71.6 (DO), U75.1 (DI)
unnamed: U72.5 (CO), U76.2 (CI)
unnamed: U72.6 (DO), U76.1 (DI)
unnamed: U73.5 (CO), U77.2 (CI)
unnamed: U73.6 (DO), U77.1 (DI)
unnamed: U8.13 (D2), U100.3 (OUTPUT)
unnamed: U8.12 (D1), U101.3 (OUTPUT)
unnamed: U8.11 (D0), U102.3 (OUTPUT)
unnamed: U9.6 (D7), U103.3 (OUTPUT)
unnamed: U9.5 (D6), U104.3 (OUTPUT)
unnamed: U9.4 (D5), U105.3 (OUTPUT)
unnamed: U9.3 (D4), U106.3 (OUTPUT)
unnamed: U9.14 (D3), U107.3 (OUTPUT)
unnamed: U9.13 (D2), U108.3 (OUTPUT)
unnamed: U9.12 (D1), U109.3 (OUTPUT)
unnamed: U9.11 (D0), U110.3 (OUTPUT)

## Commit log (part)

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2026-04-28 Documentation for every module
2026-06-10 Initial readme
2026-06-11 Current version of the 3D model
2026-06-11 Adding chess piece designs via laptop
2026-06-13 V1 Code
    First fully builded version with no errors
2026-06-13 V1 Code sorted
2026-06-13 Removed files
2026-06-13 Updated chess pieces
2026-06-13 Updated hardware file
2026-06-13 Updated hardware folder
2026-06-14 Before submit commit
2026-06-14 Remove files
2026-06-14 Include gitignore
2026-06-14 One last picture
2026-06-15 firstpart
2026-06-15 secoond part
2026-06-15 Third commit
2026-06-15 Pictures
2026-06-15 Components
2026-06-15 Project status updated
2026-06-15 Readme updated
2026-06-15 Zine in pdf form
2026-06-15 ONE FINAL COMMIT (Hopefully)
2026-06-15 forgot theese
2026-06-15 BOM fix
2026-06-15 Fixed from soup recommendation
2026-06-15 removed 7z
2026-06-15 added zip instead of 7z
2026-06-15 Added the step files that i've forgotten
2026-06-15 Fixed some errors and finished BOM
2026-06-15 small fix
2026-06-16 Small add-in+fix
2026-06-16 Updated url
2026-06-16 Improved Schematic visuals
2026-06-16 hopefully final commit
2026-06-16 small notice
2026-06-16 Small iteration
2026-06-17 Step variants of 3D printing
2026-06-17 Added .step file version
2026-06-17 Fully assembled .step
2026-06-18 Picture fix
2026-06-18 Modified resistors
2026-06-18 Fix for submission
2026-06-20 Added pulups to hall effect
2026-06-21 forgot to change print
2026-06-21 Had an excess voltage divider
2026-06-22 Updated step from previous

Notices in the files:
README.md:
License:
This project is licensed under the **MIT License** - see [LICENSE](LICENSE) for full terms.
Chess engine: [mcu-max](https://github.com/Gissio/mcu-max) - MIT License
